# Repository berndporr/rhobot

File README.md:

# RhoBot: A Robotics and AI platform

RhoBot is a mobile robot for research in obstacle avoidance built using an NVIDIA Jetson Nano, a Slamtec A1M8 RPLiDAR, a Raspberry Pi Cam v2, and two Parallax CR serco motors. The API provided in this repo provides an abstracted way to interface with the motors, however does not currently support interface with the LiDAR or camera so these would need to be implemented by a user.

## Table of contents

- Bill of Sale
- Enclosure and PCB Manufacture
- Build Guide and Set Up
- API Installation
- Sample Programs
- Credits

## Bill of Sale

| Part | Quantity | Cost (VAT included) | Where to buy |
| -------- | ------- | ------- | ------- |
| NVIDIA Jetson Nano | x1 | £167.94 | [RS Components](https://uk.rs-online.com/web/p/processor-development-tools/1999831?gb=s) |
| Parallax CR Servo Motor | x2 | £40.00 | [RS Components](https://uk.rs-online.com/web/p/servo-motors/7813046?gb=s) |
| Parallax Wheels | x2 | £6.40 | [Parallax](https://www.parallax.com/product/robot-wheel-molded-tire-for-servos/) |
| Ansmann Power Supply | x1 | £31.51 | [RS Components](https://uk.rs-online.com/web/p/power-banks/2498449?gb=s) |
| USB-A to DC Jack Cable | x2 | £12.84 | [RS Components](https://uk.rs-online.com/web/p/usb-cables/1862796?gb=s) |
| A1M8 LiDAR | x1 | £83.60 | [RobotShop](https://uk.robotshop.com/products/rplidar-a1m8-360-degree-laser-scanner-development-kit) |
| Raspberry Pi Camera v2 | x2 | £18.61 | [RS Components](https://uk.rs-online.com/web/p/raspberry-pi-cameras/9132664?gb=s) |
| USB Wifi Adapter | x1 | £12.00 | [RS Components](https://uk.rs-online.com/web/p/wifi-adapters/2558455?gb=s) |
| Total | ------- | £372.90 | ------- |

Necessary screws, nuts and bolts are not included in the bill of sale.

## Enclosure and PCB Manufacture

The enclosure is a three teir design and is fully 3D printable. In the CAD directory the their teirs are available in full and split to allow for printing on a smaller printer. The total print time is between 28 - 37 hours depending on material, and around £9 of filament. The weight is 0.3 kg.

If access to a 3D printer is not possible, the service [CraftCloud](craftcloud3d.com) have quoted £23.38 for the manufacture of the enclosure in PLA plastic.

The design files for the PCB were made using KiCAD and are available in the PCB directory. The service [PCBWay](pcbway.com) has quoted £4.01 for the manufacture of 10 boards.

## Build Guide and Set up

### Solder PCB
Firstly, sockets should be soldered onto the custom PCB. The 40 pin socket should be soldered to the bottom of the board and the remaining sockets should be mounted to the top of the board.

### Lowest Level
1) Screw the wheels onto the motors.
2) Use nuts and bolts to attach both motors to the "lower" enclosure component in the four mounting holes. Ensure the cables of the motors point towards the front of the enclosure so they will line up with the center of the LiDAR.
3) Use bolts screws to attach the camera to the mount on the "lower" component and route it's cable to the back of the enclosure.
4) Rest the power supply on top of the motors with the ports facing the back of the enclosure. Connect the USB-A to DC cables to the USB ports of the supply.

### Middle Level
1) Use bolts to secure the Jetson to the lower standoffs of the "middle" enclosure component.
2) Use boolts to secure the LiDAR sensor to the higher standoffs of the "middle" component.
3) Attach the PCB to the 40 pin GPIO header of the Jetson.
4) Route the motors and camera wire through the slots in the "middle" component. Attach the camera cable to the CSI port of the Jetson. Attach the motors to the PCB using the relevant sockets, noting the circuit schematic.
5) Connect the LiDAR UART and motor cables to the PCB noting the schematic.
6) Place the "middle" component over the "lower" component.

### Upper Level
1) Place the "upper" component onto the "middle" componet and secure the enclosure with the sixe bolt holes around the perimeter.
2) Attach the USB Wifi adapter to a USB port on the Jetson
3) Connect the power supply to the Jetson and PCB through using the USB to DC cables.

### Jetson Set Up
For detailed instructions how how to set up the Jetson, click this [link](https://developer.nvidia.com/embedded/learn/get-started-jetson-nano-devkit).

Once the Jetson boots, connect to a wireless network using the Linux network manager.

## API Installation

### Dependencies
Clone and build the [JetsonGPIO](https://github.com/pjueon/JetsonGPIO) repository. This will install the library used to interface with the Jetson's GPIO header.

For the camer and LiDAR, the [jetson-inference]()https://github.com/dusty-nv/jetson-inference and [rplidar-sdk](https://github.com/Slamtec/rplidar_sdk) are recommended respectively.

### Build Project
Clone this repository and run the following commands to build the project:

`mkdir build && cd build`

`cmake ..`

`make`

This will build the API library and compile the sample programs.

## Sample Programs

sample programs are provided to test the motor interface. To execute them run the relevant of the following commands while in the build directory:

`./test_motors`

`./test_differential_steering`

`./test_lidar`

## Credits

This project has been supervised by Dr. Bernd Porr and is a continuation of work done on the [AlphaBot](https://github.com/berndporr/alphabot) and [SigmaBot](https://github.com/berndporr/sigmabot) projects.

RhoBot is ©️ copyright 2024 of J.C. Redmond III and any use of the material in this repository should be appropriately credited.

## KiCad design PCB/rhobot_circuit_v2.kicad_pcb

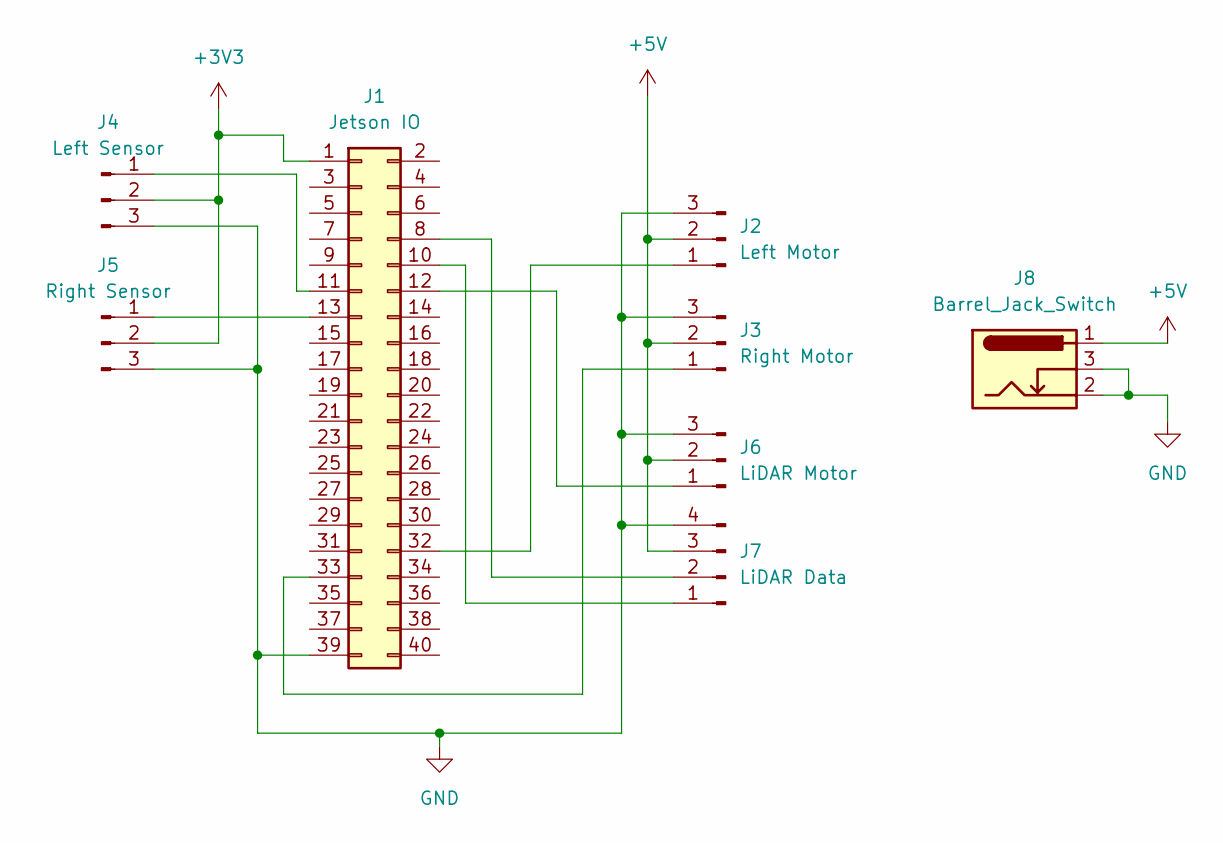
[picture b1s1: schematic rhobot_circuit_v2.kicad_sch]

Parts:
J1: Jetson IO; PinSocket_2x20_P2.54mm_Vertical
J2: Left Motor; PinHeader_1x03_P2.54mm_Vertical
J3: Right Motor; PinHeader_1x03_P2.54mm_Vertical
J4: Left Sensor; PinHeader_1x03_P2.54mm_Vertical
J5: Right Sensor; PinHeader_1x03_P2.54mm_Vertical
J6: LiDAR Motor; PinHeader_1x03_P2.54mm_Vertical
J7: LiDAR Data; PinHeader_1x04_P2.54mm_Vertical
J8: Barrel_Jack_Switch; BarrelJack_Horizontal

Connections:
+3V3: J1.1, J4.2, J5.2
+5V: J2.2, J3.2, J6.2, J7.3, J8.1
GND: J1.39, J2.3, J3.3, J4.3, J5.3, J6.3, J7.4, J8.2, J8.3
unnamed: J1.8, J7.2
unnamed: J1.10, J7.1
unnamed: J1.11, J4.1
unnamed: J1.12, J6.1
unnamed: J1.13, J5.1
unnamed: J1.32, J2.1
unnamed: J1.33, J3.1

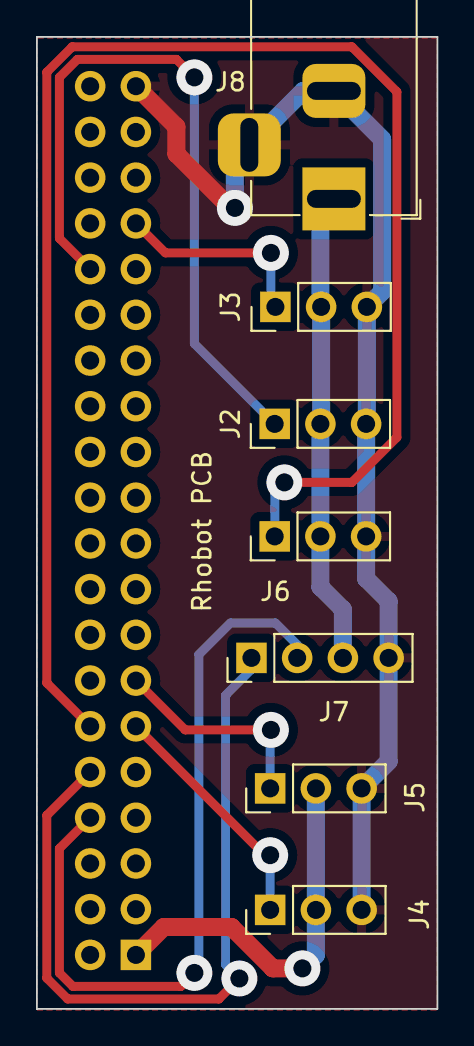
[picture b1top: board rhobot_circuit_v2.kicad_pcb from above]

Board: 2 copper layers, 22.2 x 54.0 mm, 8 parts (1 on the bottom side), 10 nets.

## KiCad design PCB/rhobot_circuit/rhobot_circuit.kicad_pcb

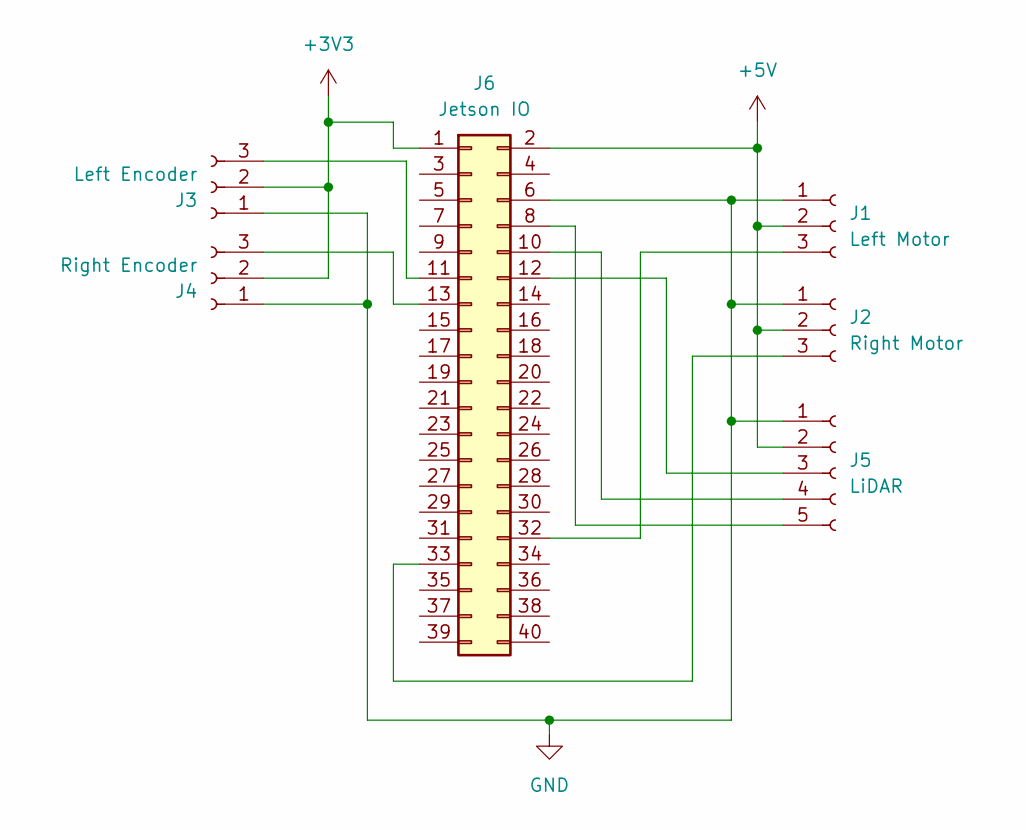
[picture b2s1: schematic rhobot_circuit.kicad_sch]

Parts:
J1: Left Motor; PinSocket_1x03_P2.54mm_Vertical
J2: Right Motor; PinSocket_1x03_P2.54mm_Vertical
J3: Left Encoder; PinSocket_1x03_P2.54mm_Vertical
J4: Right Encoder; PinSocket_1x03_P2.54mm_Vertical
J5: LiDAR; PinSocket_1x05_P2.54mm_Vertical
J6: Jetson IO; PinSocket_2x20_P2.54mm_Vertical

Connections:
+3V3: J3.2, J4.2, J6.1
+5V: J1.2, J2.2, J5.2, J6.2
GND: J1.1, J2.1, J3.1, J4.1, J5.1, J6.6
unnamed: J1.3, J6.32
unnamed: J2.3, J6.33
unnamed: J3.3, J6.11
unnamed: J4.3, J6.13
unnamed: J5.3, J6.12
unnamed: J5.4, J6.10
unnamed: J5.5, J6.8

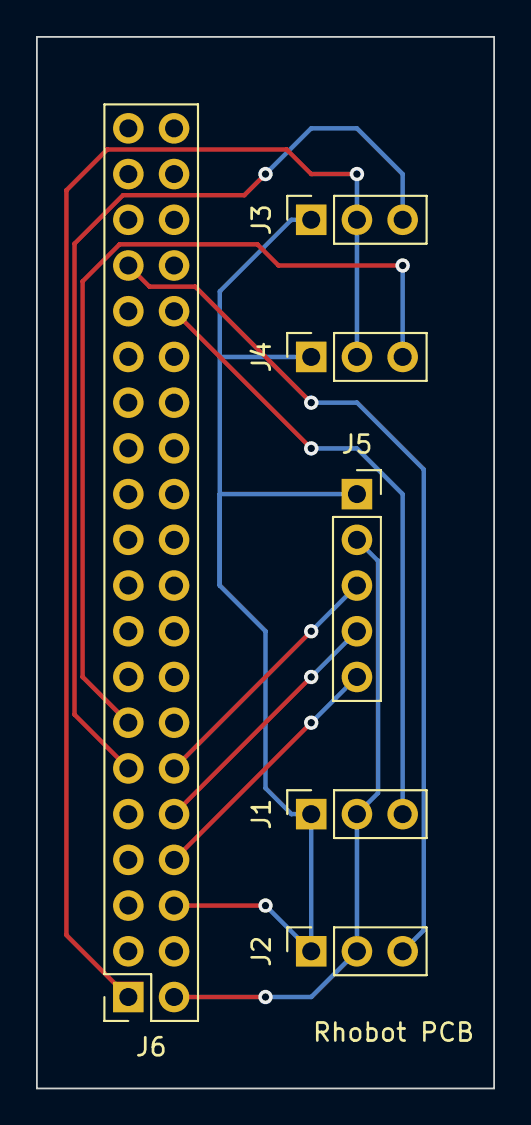
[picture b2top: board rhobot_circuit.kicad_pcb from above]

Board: 2 copper layers, 25.4 x 58.4 mm, 6 parts (0 on the bottom side), 10 nets.

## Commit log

2024-01-19 test commit
2024-01-19 added git ignore
2024-01-20 gpio in test built w cmake
2024-01-25 simple calibrated motor test
2024-02-18 photomask
2024-03-12 pwm working on pcb
2024-03-13 better cmake architecture
2024-03-13 motor test
2024-03-13 start of the api
2024-03-14 API wokring for motor control
2024-03-14 motor test code
2024-03-15 differential steering working
2024-03-15 updated steering test
2024-03-27 git ignore build
2024-03-29 soft pwm control
2024-03-29 git ignore
2024-03-29 oops
2024-04-04 tested camera
2024-04-08 cam test
2024-04-09 clean up
2024-04-10 cam test comment
2024-04-10 radius not diameter
2024-04-10 soft pwm optimisation
2024-04-10 off time for soft pwm!
2024-04-12 working soft pwm
2024-04-12 soft pwm freq
2024-04-12 Updated CAD
2024-04-14 figs for readme
